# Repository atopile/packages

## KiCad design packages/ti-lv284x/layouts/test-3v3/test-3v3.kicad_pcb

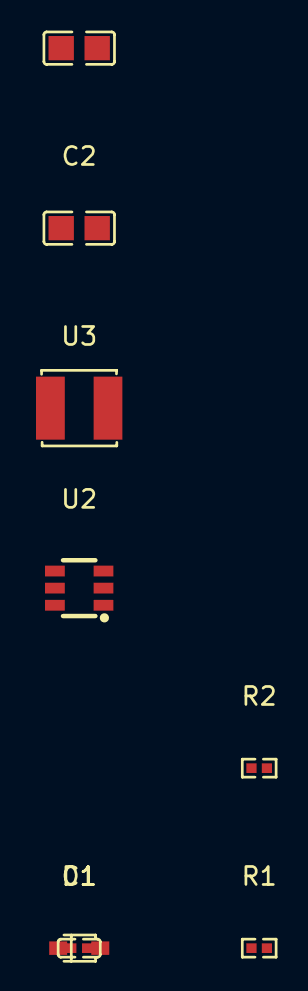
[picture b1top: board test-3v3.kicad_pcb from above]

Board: 2 copper layers, 8 parts (0 on the bottom side), 7 nets, no tracks yet.

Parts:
C1: 470nF ±20% 16V X5R; C0402
C2: 4.7µF ±10% 25V X5R; C0805
C3: 10µF ±10% 25V X5R; C0805
D1: SOD-323_L1.8-W1.3-LS2.5-RD
R1: 10kΩ ±1% 62.5mW; R0402
R2: 33kΩ ±1% 62.5mW; R0402
U2: SOT-23-6_L2.9-W1.6-P0.95-LS2.8-BR
U3: IND-SMD_L4.0-W4.0

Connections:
CB: C1.1, U2.1
FB: R1.1, R2.2, U2.3
cathode: C1.2, D1.1, U2.6
hv: C3.1, R2.1
nSHDN: C2.1, U2.4, U2.5
regulator-gnd: C3.2, D1.2, R1.2
regulator-gnd-1: C2.2, U2.2

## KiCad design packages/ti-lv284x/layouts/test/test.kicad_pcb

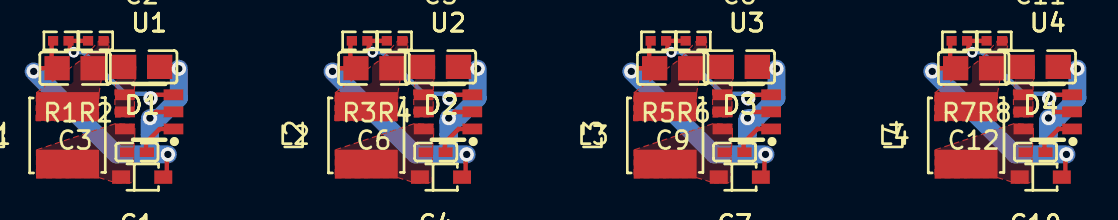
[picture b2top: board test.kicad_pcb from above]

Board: 2 copper layers, 32 parts (0 on the bottom side), 24 nets.

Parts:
C1, C4, C7, C10: 470nF ±20% 16V X5R; C0402
C2, C5, C8, C11: 4.7µF ±10% 25V X5R; C0805
C3, C6, C9, C12: 10µF ±10% 25V X5R; C0805
D1, D2, D3, D4: SOD-323_L1.8-W1.3-LS2.5-RD
L1, L2, L3, L4: IND-SMD_L4.0-W4.0
R1, R3, R8: 10kΩ ±1% 62.5mW; R0402
R2, R6: 100kΩ ±1% 62.5mW; R0402
R4: 51kΩ ±1% 62.5mW; R0402
R5: 33kΩ ±1% 62.5mW; R0402
R7: 8.2kΩ ±1% 62.5mW; R0402
U1, U2, U3, U4: SOT-23-6_L2.9-W1.6-P0.95-LS2.8-BR

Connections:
regulators[0]-CB: C1.1, U1.1
regulators[0]-FB: R1.1, R2.2, U1.3
regulators[0]-K: C1.2, D1.1, L1.1, U1.6
regulators[0]-VIN: C2.1, U1.4, U1.5
regulators[0]-gnd: C2.2, C3.2, D1.2, R1.2, U1.2
regulators[0]-hv: C3.1, L1.2, R2.1
regulators[1]-CB: C4.1, U2.1
regulators[1]-FB: R3.1, R4.2, U2.3
regulators[1]-K: C4.2, D2.1, L2.1, U2.6
regulators[1]-VIN: C5.1, U2.4, U2.5
regulators[1]-gnd: C5.2, C6.2, D2.2, R3.2, U2.2
regulators[1]-hv: C6.1, L2.2, R4.1
regulators[2]-CB: C7.1, U3.1
regulators[2]-FB: R5.1, R6.2, U3.3
regulators[2]-K: C7.2, D3.1, L3.1, U3.6
regulators[2]-VIN: C8.1, U3.4, U3.5
regulators[2]-gnd: C8.2, C9.2, D3.2, R5.2, U3.2
regulators[2]-hv: C9.1, L3.2, R6.1
regulators[3]-CB: C10.1, U4.1
regulators[3]-FB: R7.1, R8.2, U4.3
regulators[3]-K: C10.2, D4.1, L4.1, U4.6
regulators[3]-VIN: C11.1, U4.4, U4.5
regulators[3]-gnd: C11.2, C12.2, D4.2, R7.2, U4.2
regulators[3]-hv: C12.1, L4.2, R8.1

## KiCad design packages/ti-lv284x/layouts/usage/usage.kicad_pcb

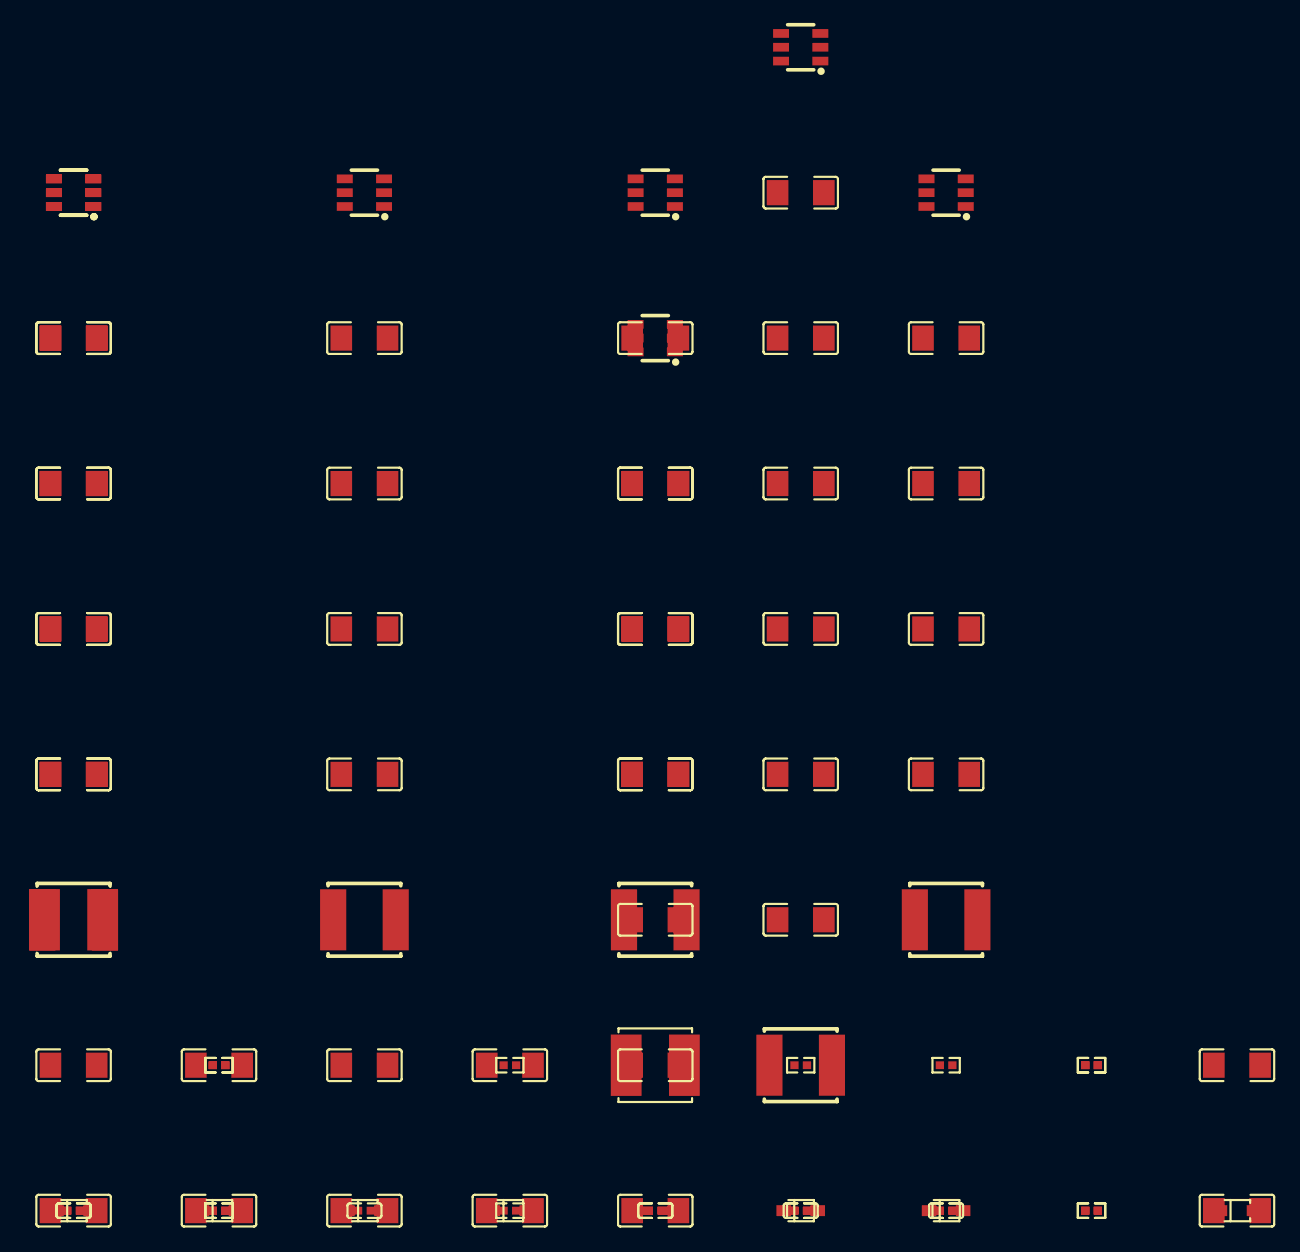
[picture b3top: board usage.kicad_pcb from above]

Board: 2 copper layers, 84 parts (0 on the bottom side), 42 nets, no tracks yet.

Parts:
C1, C11, C16, C21, C26, C31, C41: 470nF ±20% 16V X5R; C0402
C2, C12, C17, C22, C27, C32, C42: 4.7µF ±10% 100V X7S; C1206
C3, C4, C5, C6, C7, C8, C9, C10, C13, C14, C15, C18, C19, C20, C23, C24, C25, C28, C29, C30, C33, C34, C35, C36, C37, C38, C39, C40, C43, C44, C45, C46, C47, C48, C49: 10µF ±10% 50V X5R; C1206
D1, D2, D3, D4, D5, D6, D7: SOD-323_L1.8-W1.3-LS2.5-RD
L1: 10µH ±20% 2.1A 83mΩ; IND-SMD_L5.0-W5.0
L2, L4, L5: 100µH ±20% 780mA 728mΩ; IND-SMD_L5.0-W5.0_FNR50XXS
L3: 470µH ±20% 400mA 3.9Ω; IND-SMD_L5.0-W5.0_FNR50XXS
L6: 47µH ±20% 1.15A 354mΩ; IND-SMD_L5.0-W5.0_FNR50XXS
L7: 22µH ±20% 1.6A 168mΩ; IND-SMD_L5.0-W5.0_H4.0
R1, R3, R5, R7, R9, R11, R13: 10kΩ ±1% 62.5mW; R0402
R2: 120kΩ ±1% 62.5mW; R0402
R4: 100kΩ ±0% 62.5mW; R0402
R6: 56kΩ ±1% 62.5mW; R0402
R8: 150kΩ ±1% 62.5mW; R0402
R10: 510Ω ±1% 62.5mW; R0402
R12: 180kΩ ±1% 62.5mW; R0402
R14: 470kΩ ±1% 62.5mW; R0402
U1, U2, U3, U4, U5, U6, U7: SOT-23-6_L2.9-W1.6-P0.95-LS2.8-BR

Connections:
regulator40_5v-CB: C11.1, U3.1
regulator40_5v-FB: R5.1, R6.2, U3.3
regulator40_5v-VIN: C12.1, U3.4, U3.5
regulator40_5v-cathode: C11.2, D1.1, L3.1, U3.6
regulator40_5v-gnd: C6.2, C7.2, C12.2, C13.2, C14.2, C15.2, D1.2, R5.2, U3.2
regulator40_5v-hv: C6.1, C7.1, C13.1, C14.1, C15.1, L3.2, R6.1
regulator41_12v-CB: C16.1, U4.1
regulator41_12v-FB: R7.1, R8.2, U4.3
regulator41_12v-VIN: C17.1, U4.4, U4.5
regulator41_12v-cathode: C16.2, D2.1, L4.1, U4.6
regulator41_12v-gnd: C8.2, C9.2, C17.2, C18.2, C19.2, C20.2, D2.2, R7.2, U4.2
regulator41_12v-hv: C8.1, C9.1, C18.1, C19.1, C20.1, L4.2, R8.1
regulator42_0v8-CB: C21.1, U5.1
regulator42_0v8-FB: R9.1, R10.2, U5.3
regulator42_0v8-VIN: C22.1, U5.4, U5.5
regulator42_0v8-cathode: C21.2, D3.1, L5.1, U5.6
regulator42_0v8-gnd: C10.2, C22.2, C23.2, C24.2, C25.2, C36.2, D3.2, R9.2, U5.2
regulator42_0v8-hv: C10.1, C23.1, C24.1, C25.1, C36.1, L5.2, R10.1
regulator42_15v-CB: C26.1, U6.1
regulator42_15v-FB: R11.1, R12.2, U6.3
regulator42_15v-VIN: C27.1, U6.4, U6.5
regulator42_15v-cathode: C26.2, D4.1, L6.1, U6.6
regulator42_15v-gnd: C27.2, C28.2, C29.2, C30.2, C37.2, C38.2, D4.2, R11.2, U6.2
regulator42_15v-hv: C28.1, C29.1, C30.1, C37.1, C38.1, L6.2, R12.1
regulator42_35v-CB: C31.1, U7.1
regulator42_35v-FB: R13.1, R14.2, U7.3
regulator42_35v-VIN: C32.1, U7.4, U7.5
regulator42_35v-cathode: C31.2, D5.1, L7.1, U7.6
regulator42_35v-gnd: C32.2, C33.2, C34.2, C35.2, C39.2, C40.2, D5.2, R13.2, U7.2
regulator42_35v-hv: C33.1, C34.1, C35.1, C39.1, C40.1, L7.2, R14.1
regulator42_big_inductor-VIN: C42.1, U2.4, U2.5
regulator42_big_inductor-gnd: C42.2, C43.2, C44.2, C45.2, C46.2, C47.2, D6.2, R3.2, U2.2
regulator42_big_inductor-hv: C43.1, C44.1, C45.1, C46.1, C47.1, L2.2, R4.1
regulator42_big_inductor.regulator-CB: C41.1, U2.1
regulator42_big_inductor.regulator-FB: R3.1, R4.2, U2.3
regulator42_big_inductor.regulator-cathode: C41.2, D6.1, L2.1, U2.6
regulator42_small_inductor-CB: C1.1, U1.1
regulator42_small_inductor-FB: R1.1, R2.2, U1.3
regulator42_small_inductor-VIN: C2.1, U1.4, U1.5
regulator42_small_inductor-cathode: C1.2, D7.1, L1.1, U1.6
regulator42_small_inductor-gnd: C2.2, C3.2, C4.2, C5.2, C48.2, C49.2, D7.2, R1.2, U1.2
regulator42_small_inductor-hv: C3.1, C4.1, C5.1, C48.1, C49.1, L1.2, R2.1

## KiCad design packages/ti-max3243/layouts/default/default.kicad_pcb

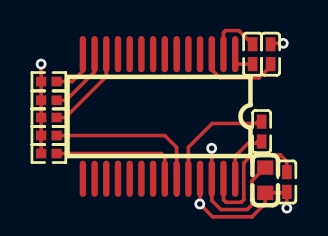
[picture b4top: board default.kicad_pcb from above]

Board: 2 copper layers, 11 parts (0 on the bottom side), 13 nets.

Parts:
C1, C2, C3, C4: 1e-06F; C0402
C5: 1e-06F; C0603
R1, R2, R3, R4, R5: 10000Ω; R0402
U1: SSOP-28_L10.2-W5.3-P0.65-LS7.8-BL

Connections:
DTR: R3.1, U1.14
FORCEON: R1.1, U1.23
charge_pump_caps[1]-power-hv: C2.1, U1.1
charge_pump_caps[1]-power-lv: C2.2, U1.2
charge_pump_caps[2]-power-hv: C3.1, U1.27
charge_pump_caps[3]-power-hv: C4.1, U1.3
hv: C1.1, U1.28
lv: C1.2, U1.24
nFORCEOFF: R2.1, U1.22
power_decoupling-power-hv: C5.1, R1.2, R2.2, R3.2, R4.2, R5.2, U1.26
power_decoupling-power-lv: C3.2, C4.2, C5.2, U1.25
uart-RTS: R5.1, U1.12
uart-TX: R4.1, U1.13
